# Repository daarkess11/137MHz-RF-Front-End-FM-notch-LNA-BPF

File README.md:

# 137MHz-VHF-Front-End (Work-in-Progress)

137.5 MHz VHF Downlink RF Front-End for satellite ground stations.

## Quick specs

| Parameter | Value |
|---|---|
| Target frequency | 137.5 MHz VHF Downlink (NOAA-15/18/19, Meteor-M) |
| Active device | PGA-103+ E-PHEMT MMIC |
| Cascaded gain (S21) | 22 dB @ 137 MHz |
| Noise Figure (NF) | ~1.84 dB *(simulation/analytical estimate only, not experimentally measured!!)* |
| Out-of-band rejection (88–108 MHz) | -33.3 dB to -48.8 dB (cascaded) |
| Stability | Unconditionally stable 10 MHz – 4 GHz (R+L shunt)¹ |
| PCB | CPWG (50 Ω), W=1.25mm, H=1.6mm, S=0.24mm, εr=4.5, t=1oz (35µm) |

¹*Above the available .s2p model limits, the stability curves rely on simulator extrapolation and should be treated as indicative rather than physically validated results. See the stability section in the full report for the modelling limitations.*

## Design Approach

- **Simulation:** QUCS-S with real component S-parameters
- **Validation:** Experimental VNA testing pending
- **EM simulation:** Not performed (CPWG geometry validated with calculator/published formulas at 137 MHz)
## Repo structure

- [`/Simulation`](./Simulation) QUCS-S files and .s2p models
- [`/hardware`](./hardware) — KiCad project files + BOM list
  
Below is a quick summary with the PCB render from KiCad and a couple of screenshots from QUCS-S with the simulation results and schematics.

## ⚠️ Prototype Status

The design has been fully simulated and theoretically verified. Experimental verification will follow once the PCB has been fabricated and tested with a VNA.

# Screenshots
*Note: I used .s2p files from the manufacturer datasheets for the simulations, not ideal component models, ideal symbols only show up when they make the schematic easier to read.*

### PCB

### S[2,1] graphic and measures (only up to 600MHz for a better view, check /docs if you want to see higher frequencies)

### Stability

## Schematics
### Cauer Notch 

### LNA

### Band-Pass Butterworth

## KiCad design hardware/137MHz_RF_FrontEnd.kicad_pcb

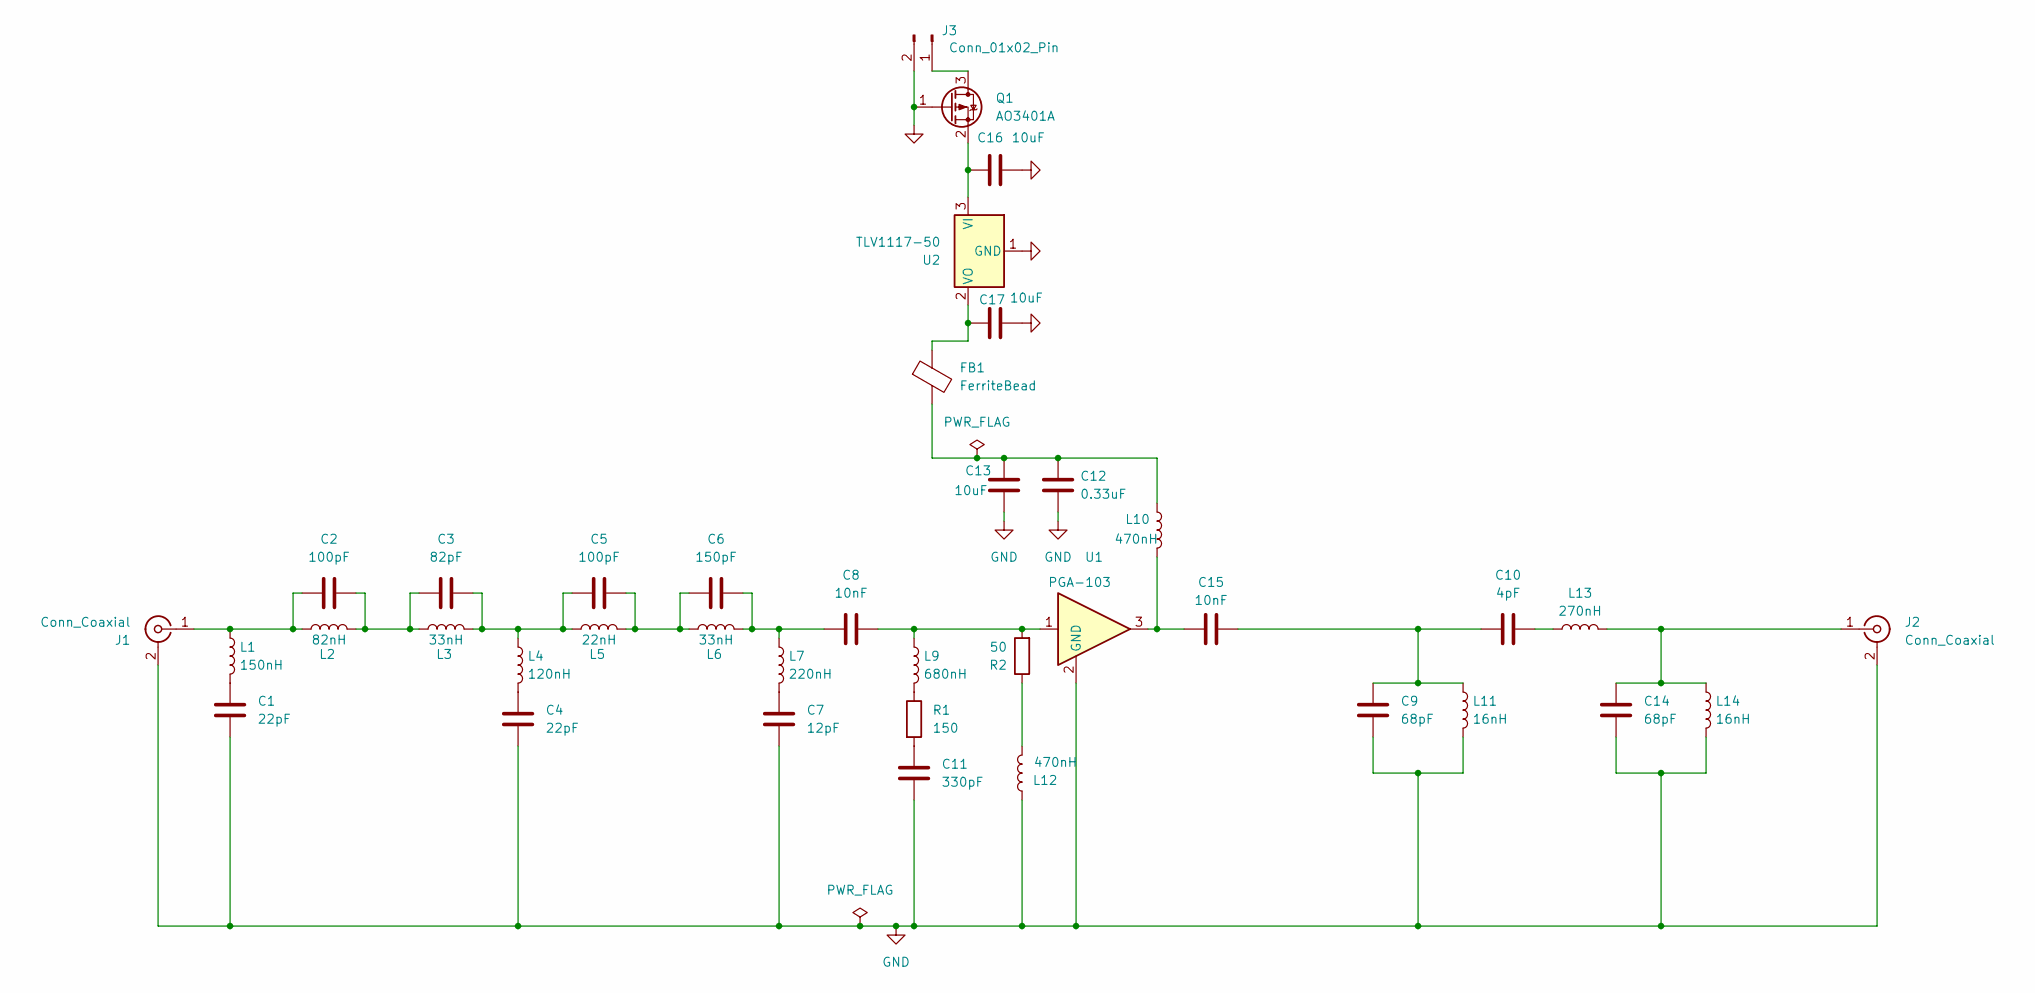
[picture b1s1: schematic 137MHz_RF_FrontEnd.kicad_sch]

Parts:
C1, C4: 22pF; C_0603_1608Metric_Pad1.08x0.95mm_HandSolder
C2, C5: 100pF; C_0603_1608Metric_Pad1.08x0.95mm_HandSolder
C3: 82pF; C_0603_1608Metric_Pad1.08x0.95mm_HandSolder
C6: 150pF; C_0603_1608Metric_Pad1.08x0.95mm_HandSolder
C7: 12pF; C_0603_1608Metric_Pad1.08x0.95mm_HandSolder
C8, C15: 10nF; C_0603_1608Metric_Pad1.08x0.95mm_HandSolder
C9, C14: 68pF; C_0603_1608Metric_Pad1.08x0.95mm_HandSolder
C10: 4pF; C_0603_1608Metric_Pad1.08x0.95mm_HandSolder
C11: 330pF; C_0603_1608Metric_Pad1.08x0.95mm_HandSolder
C12: 0.33uF; C_0805_2012Metric_Pad1.18x1.45mm_HandSolder
C13, C16, C17: 10uF; C_0805_2012Metric_Pad1.18x1.45mm_HandSolder
FB1: FerriteBead; L_0805_2012Metric_Pad1.05x1.20mm_HandSolder
J1, J2: Conn_Coaxial; SMA_Amphenol_132289_EdgeMount
J3: Conn_01x02_Pin; JST_XH_S2B-XH-A-1_1x02_P2.50mm_Horizontal
L1: 150nH; L_0603_1608Metric_Pad1.05x0.95mm_HandSolder
L2: 82nH; L_0603_1608Metric_Pad1.05x0.95mm_HandSolder
L3, L6: 33nH; L_0603_1608Metric_Pad1.05x0.95mm_HandSolder
L4: 120nH; L_0603_1608Metric_Pad1.05x0.95mm_HandSolder
L5: 22nH; L_0603_1608Metric_Pad1.05x0.95mm_HandSolder
L7: 220nH; L_0603_1608Metric_Pad1.05x0.95mm_HandSolder
L9: 680nH; L_0805_2012Metric_Pad1.05x1.20mm_HandSolder
L10, L12: 470nH; L_0805_2012Metric_Pad1.05x1.20mm_HandSolder
L11, L14: 16nH; L_0603_1608Metric_Pad1.05x0.95mm_HandSolder
L13: 270nH; L_0603_1608Metric_Pad1.05x0.95mm_HandSolder
Q1: AO3401A; SOT-23
R1: 150; R_0603_1608Metric_Pad0.98x0.95mm_HandSolder
R2: 50; R_0603_1608Metric_Pad0.98x0.95mm_HandSolder
U1: PGA-103; SOT-89-3
U2: TLV1117-50; SOT-223

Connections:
GND: C1.2, C4.2, C7.2, C9.2, C11.2, C12.2, C13.2, C14.2, C16.2, C17.2, J1.2 (Ext), J2.2 (Ext), J3.2, L11.2, L12.1, L14.2, Q1.1 (G), U1.2 (GND_2), U2.1 (GND)
unnamed: C1.1, L1.2
unnamed: C2.1, C3.2, L2.2, L3.1
unnamed: C3.1, C5.2, L3.2, L4.1, L5.1
unnamed: C4.1, L4.2
unnamed: C5.1, C6.2, L5.2, L6.1
unnamed: C6.1, C8.2, L6.2, L7.1
unnamed: C7.1, L7.2
unnamed: C8.1, L9.1, R2.2, U1.1
unnamed: C10.1, L13.1
unnamed 10: C9.1, C10.2, C15.1, L11.1; also elsewhere on the board
unnamed: C11.1, R1.2
unnamed 12: C12.1, C13.1, FB1.2, L10.1; also elsewhere on the board
unnamed 13: C15.2, L10.2, U1.3; also elsewhere on the board
unnamed: C2.2, J1.1 (In), L1.1, L2.1
unnamed: C14.1, J2.1 (In), L13.2, L14.1
unnamed: J3.1, Q1.3 (D)
unnamed: L9.2, R1.1
unnamed: L12.2, R2.1
unnamed: C16.1, Q1.2 (S), U2.3 (VI)
unnamed: C17.1, FB1.1, U2.2 (VO), U2.4

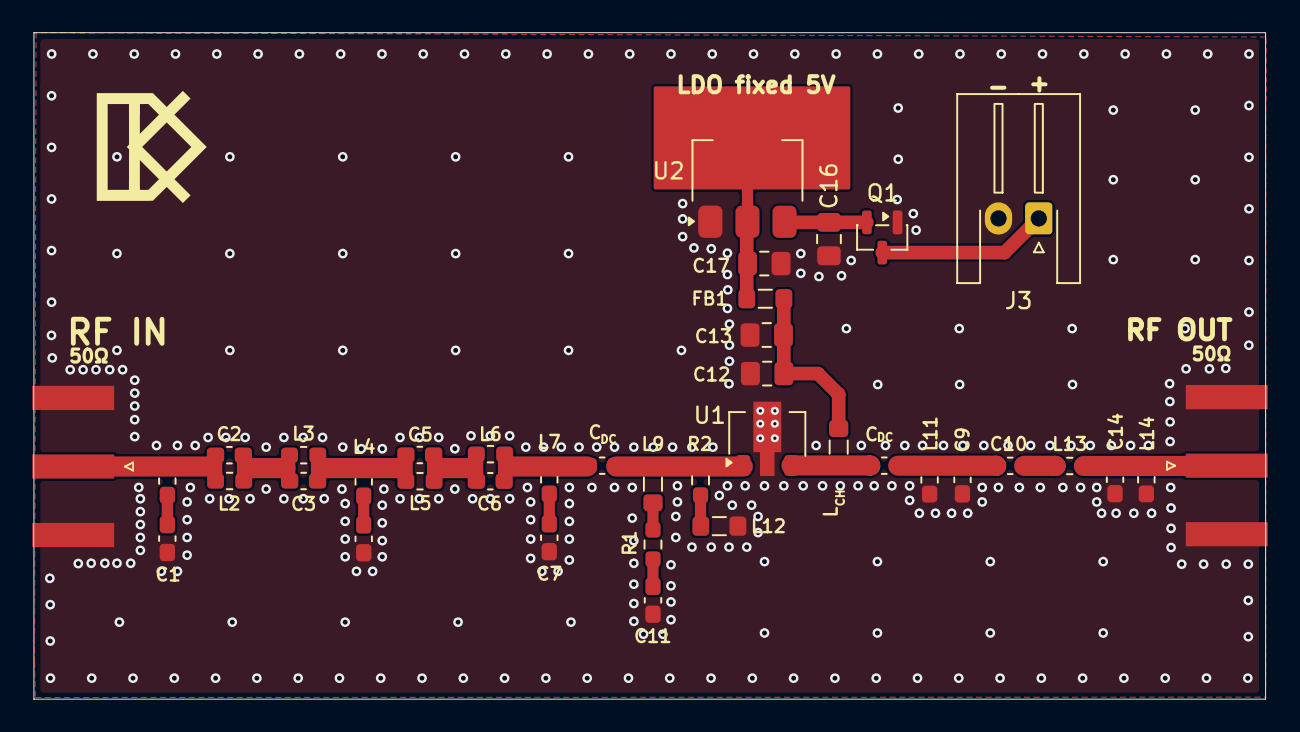
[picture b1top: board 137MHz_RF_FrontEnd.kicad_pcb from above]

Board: 2 copper layers, 76.4 x 41.3 mm, 40 parts (0 on the bottom side), 21 nets.

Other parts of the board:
-: -; LOGO
C: 10nF; C_0603_1608Metric_Pad1.08x0.95mm_HandSolder
L: 470nH; L_0805_2012Metric_Pad1.05x1.20mm_HandSolder

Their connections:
unnamed 10: C.1; also elsewhere on the board
unnamed 12: L.1; also elsewhere on the board
unnamed 13: C.2, L.2; also elsewhere on the board
